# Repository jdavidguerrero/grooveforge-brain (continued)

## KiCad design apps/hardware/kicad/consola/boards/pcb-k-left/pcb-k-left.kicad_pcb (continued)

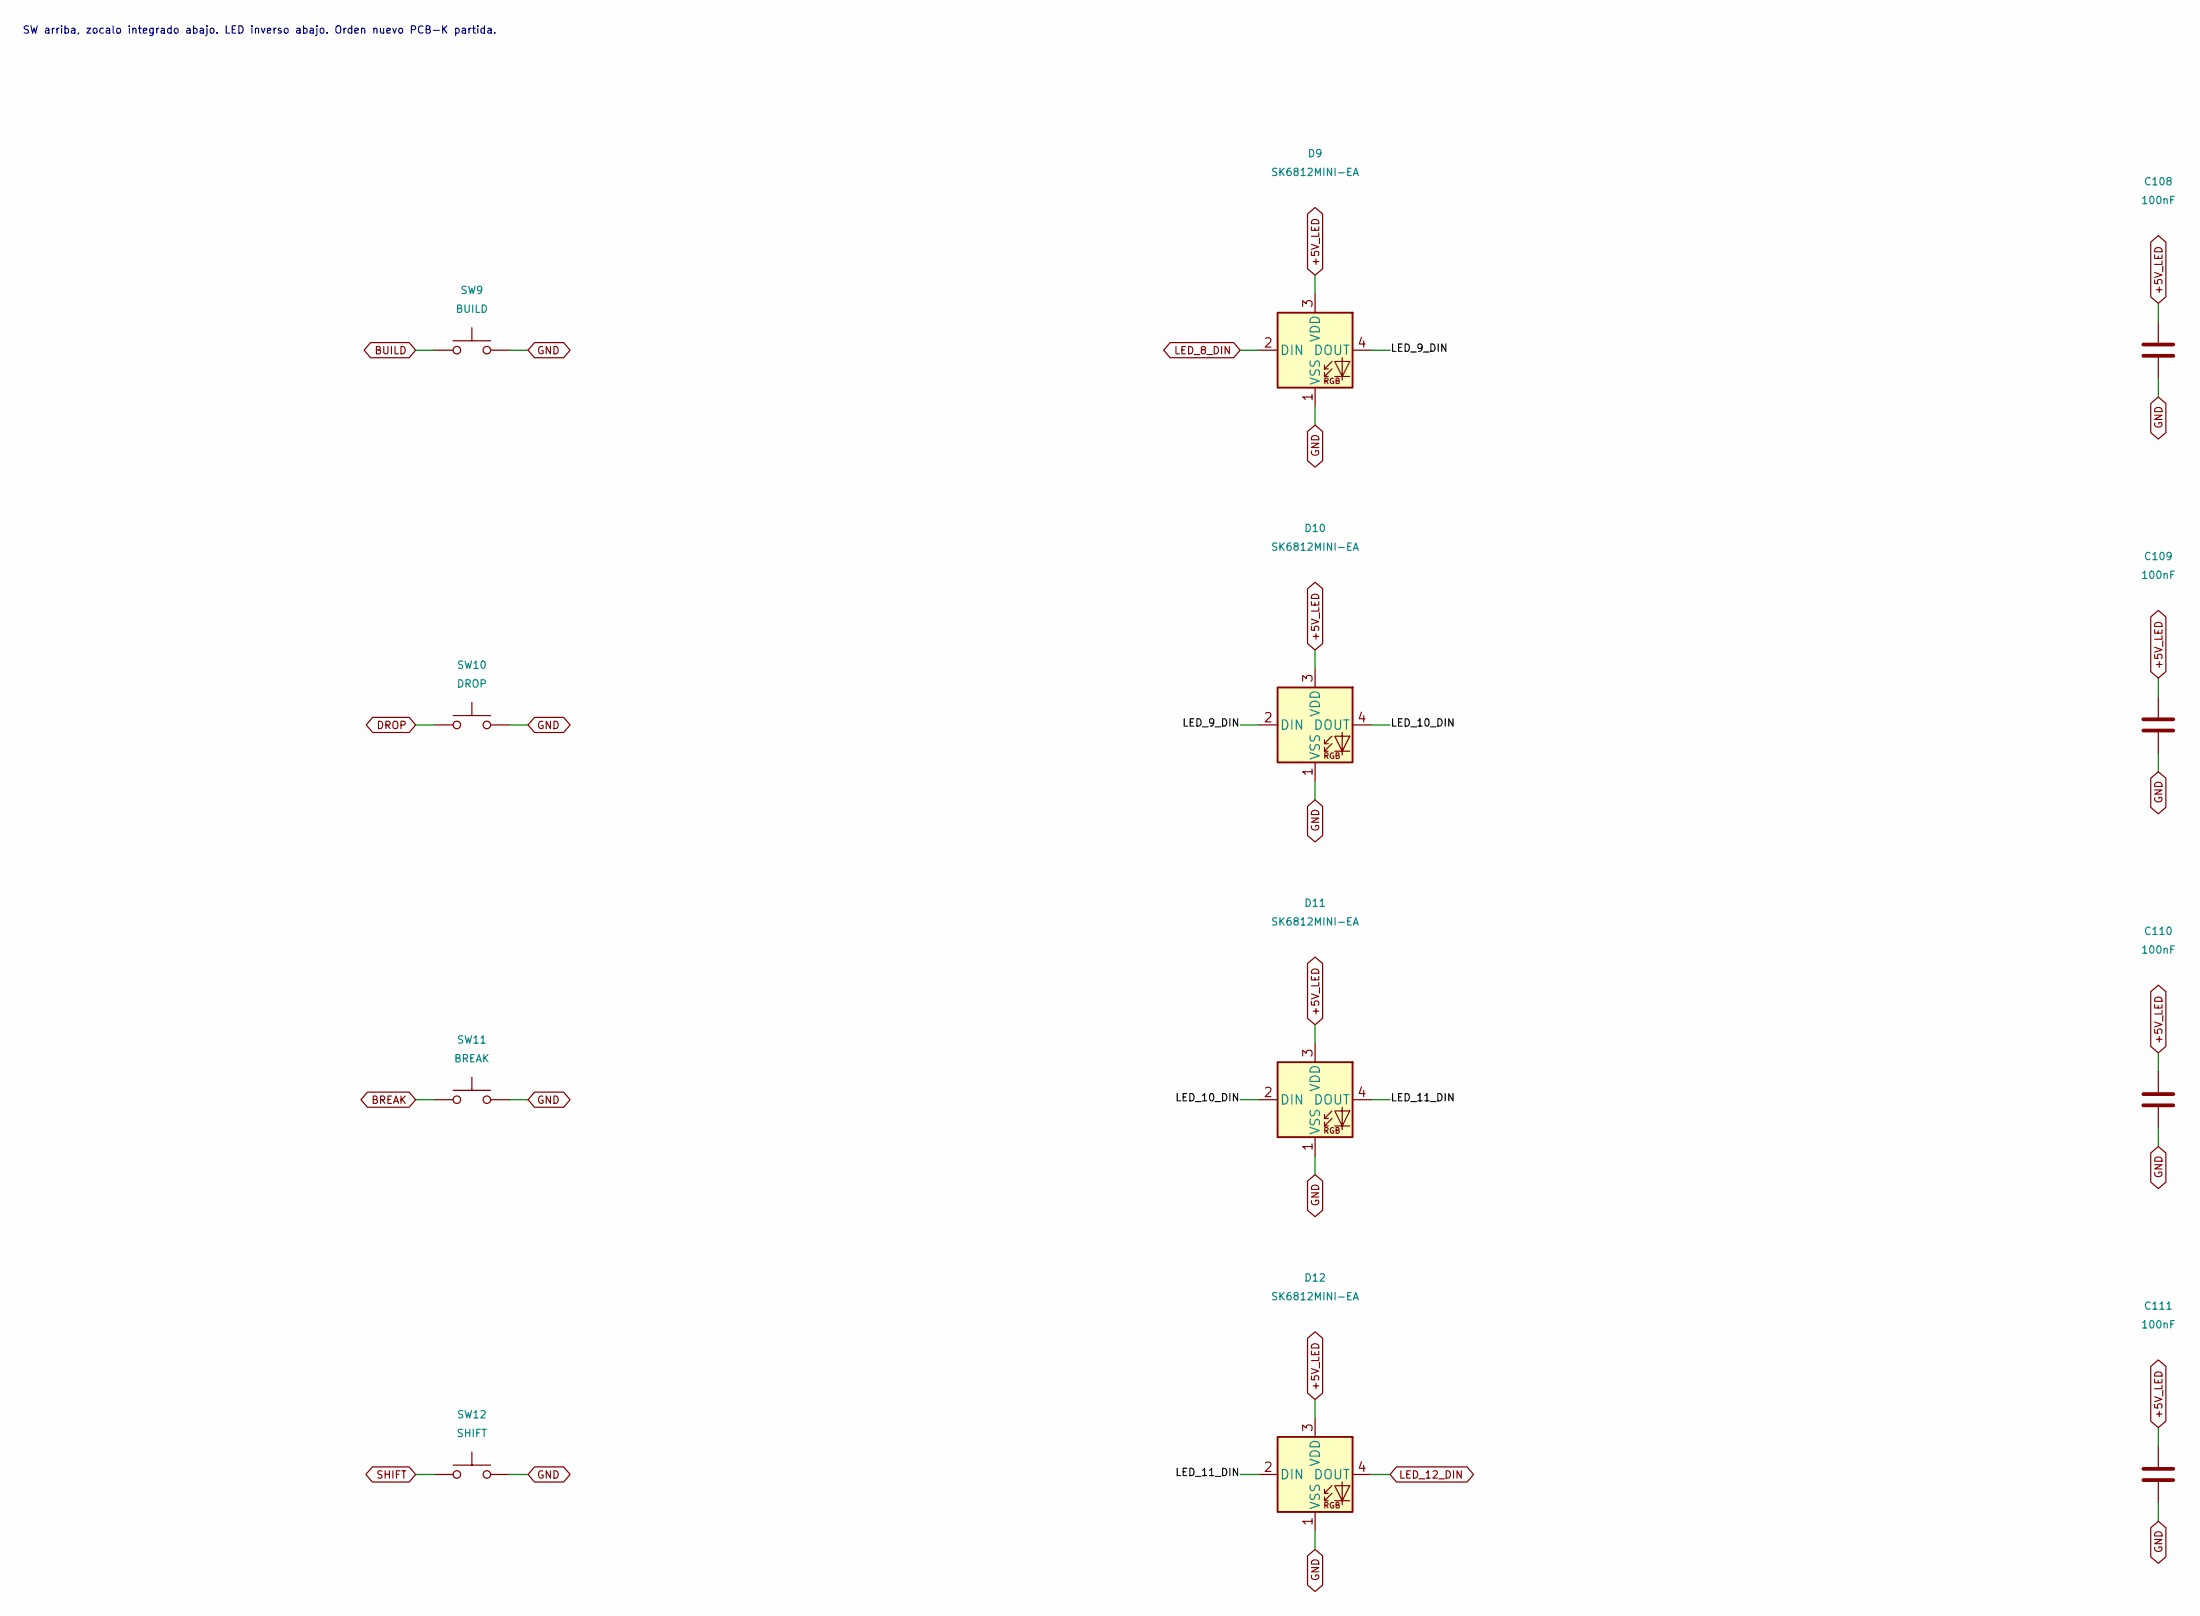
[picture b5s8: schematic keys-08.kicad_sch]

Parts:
C108, C109, C110, C111: 100nF; C_0805_2012Metric; MPN CC0805KRX7R9BB104; LCSC C49678
D9, D10, D11, D12: SK6812MINI-EA; SK6812MINI-EA_ReverseMount; MPN SK6812MINI-EA; LCSC C5378731
SW9: BUILD; Kailh_Choc_V2_PG1353_Hotswap
SW10: DROP; Kailh_Choc_V2_PG1353_Hotswap
SW11: BREAK; Kailh_Choc_V2_PG1353_Hotswap
SW12: SHIFT; Kailh_Choc_V2_PG1353_Hotswap

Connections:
+5V_LED: C108.1, C109.1, C110.1, C111.1, D9.3 (VDD), D10.3 (VDD), D11.3 (VDD), D12.3 (VDD); also elsewhere on the board
/keys-08/LED_9_DIN: D9.4 (DOUT), D10.2 (DIN)
/keys-08/LED_10_DIN: D10.4 (DOUT), D11.2 (DIN)
/keys-08/LED_11_DIN: D11.4 (DOUT), D12.2 (DIN)
BREAK: SW11.1; also elsewhere on the board
BUILD: SW9.1; also elsewhere on the board
DROP: SW10.1; also elsewhere on the board
GND: C108.2, C109.2, C110.2, C111.2, D9.1 (VSS), D10.1 (VSS), D11.1 (VSS), D12.1 (VSS), SW9.2, SW10.2, SW11.2, SW12.2; also elsewhere on the board
LED_8_DIN: D9.2 (DIN); also elsewhere on the board
LED_12_DIN: D12.4 (DOUT); also elsewhere on the board
SHIFT: SW12.1; also elsewhere on the board

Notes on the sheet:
SW arriba, zocalo integrado abajo. LED inverso abajo. Orden nuevo PCB-K partida.

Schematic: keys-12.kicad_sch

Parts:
C112, C113, C114, C115: 100nF; C_0805_2012Metric; MPN CC0805KRX7R9BB104; LCSC C49678
D13, D14, D15, D16: SK6812MINI-EA; SK6812MINI-EA_ReverseMount; MPN SK6812MINI-EA; LCSC C5378731
SW13: UNDO; Kailh_Choc_V2_PG1353_Hotswap
SW14: DELETE; Kailh_Choc_V2_PG1353_Hotswap
SW15: DUPLICATE; Kailh_Choc_V2_PG1353_Hotswap
SW16: QUANTIZE; Kailh_Choc_V2_PG1353_Hotswap

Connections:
+5V_LED: C112.1, C113.1, C114.1, C115.1, D13.3 (VDD), D14.3 (VDD), D15.3 (VDD), D16.3 (VDD); also elsewhere on the board
/keys-12/LED_13_DIN: D13.4 (DOUT), D14.2 (DIN)
/keys-12/LED_14_DIN: D14.4 (DOUT), D15.2 (DIN)
/keys-12/LED_15_DIN: D15.4 (DOUT), D16.2 (DIN)
DELETE: SW14.1; also elsewhere on the board
DUPLICATE: SW15.1; also elsewhere on the board
GND: C112.2, C113.2, C114.2, C115.2, D13.1 (VSS), D14.1 (VSS), D15.1 (VSS), D16.1 (VSS), SW13.2, SW14.2, SW15.2, SW16.2; also elsewhere on the board
LED_12_DIN: D13.2 (DIN); also elsewhere on the board
LED_16_DIN: D16.4 (DOUT); also elsewhere on the board
QUANTIZE: SW16.1; also elsewhere on the board
UNDO: SW13.1; also elsewhere on the board

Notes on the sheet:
SW arriba, zocalo integrado abajo. LED inverso abajo. Orden nuevo PCB-K partida.

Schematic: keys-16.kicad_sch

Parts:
C116: 100nF; C_0805_2012Metric; MPN CC0805KRX7R9BB104; LCSC C49678
D17: SK6812MINI-EA; SK6812MINI-EA_ReverseMount; MPN SK6812MINI-EA; LCSC C5378731
SW17: NEW; Kailh_Choc_V2_PG1353_Hotswap

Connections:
+5V_LED: C116.1, D17.3 (VDD); also elsewhere on the board
GND: C116.2, D17.1 (VSS), SW17.2; also elsewhere on the board
LED_16_DIN: D17.2 (DIN); also elsewhere on the board
LED_DATA: D17.4 (DOUT); also elsewhere on the board
NEW: SW17.1; also elsewhere on the board

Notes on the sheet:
SW arriba, zocalo integrado abajo. LED inverso abajo. Orden nuevo PCB-K partida.

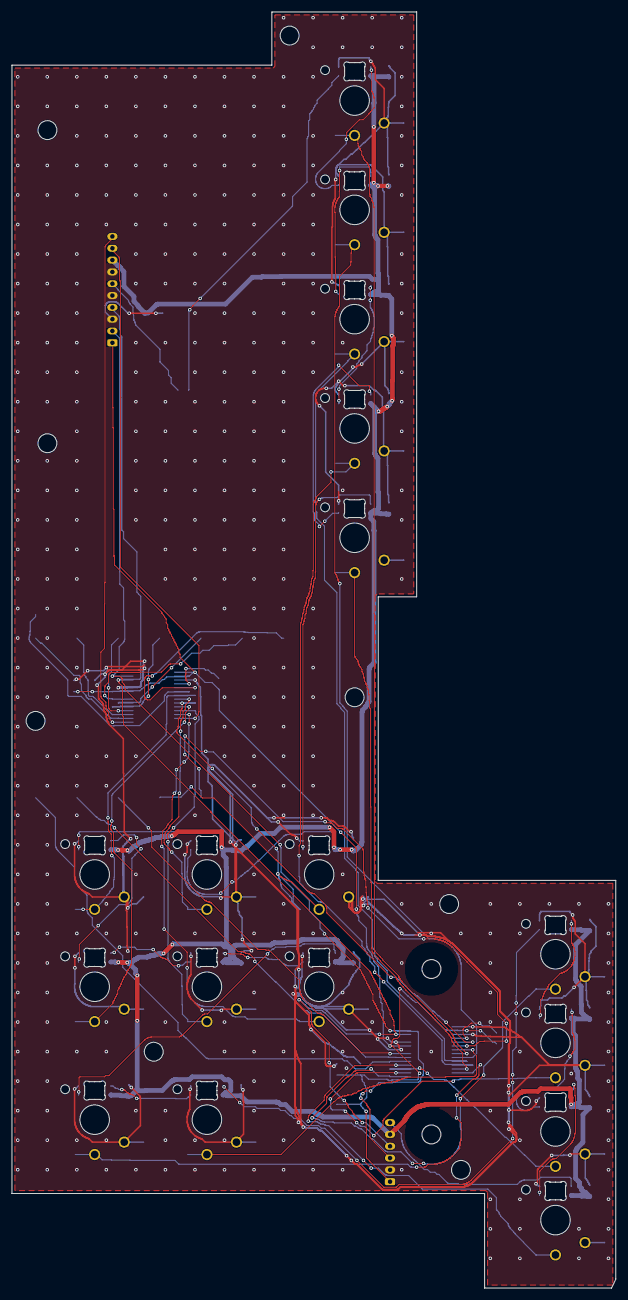
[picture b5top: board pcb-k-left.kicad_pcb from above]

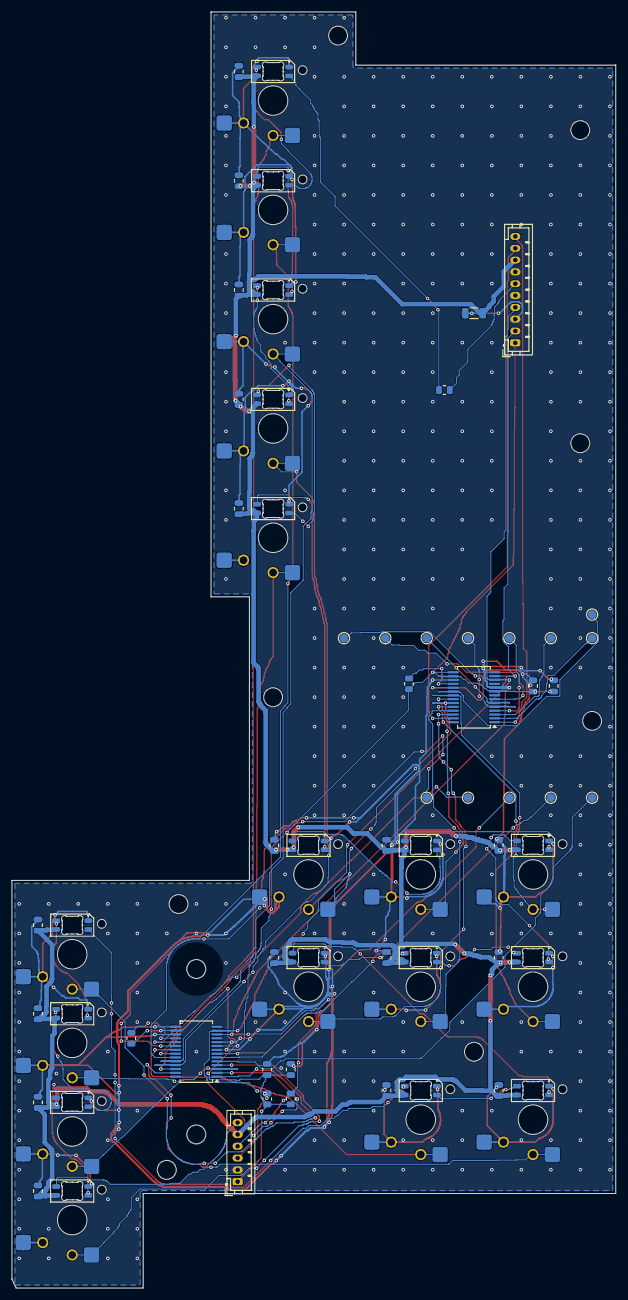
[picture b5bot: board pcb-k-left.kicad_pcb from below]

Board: 2 copper layers, 102.2 x 216.0 mm, 88 parts (61 on the bottom side), 58 nets.

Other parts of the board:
H1, H2, H3, H4, H5, H6, H7, H8, H9, H10: M2.5 PEM

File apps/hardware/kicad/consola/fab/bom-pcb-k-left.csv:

"Reference","Value","Footprint","LCSC","Supply","SupplyDescription","DNP"
"C1","22uF","Capacitor_SMD:C_1206_3216Metric","C12891","","",""
"C100","100nF","Capacitor_SMD:C_0805_2012Metric","C49678","","",""
"C101","100nF","Capacitor_SMD:C_0805_2012Metric","C49678","","",""
"C102","100nF","Capacitor_SMD:C_0805_2012Metric","C49678","","",""
"C103","100nF","Capacitor_SMD:C_0805_2012Metric","C49678","","",""
"C104","100nF","Capacitor_SMD:C_0805_2012Metric","C49678","","",""
"C105","100nF","Capacitor_SMD:C_0805_2012Metric","C49678","","",""
"C106","100nF","Capacitor_SMD:C_0805_2012Metric","C49678","","",""
"C107","100nF","Capacitor_SMD:C_0805_2012Metric","C49678","","",""
"C108","100nF","Capacitor_SMD:C_0805_2012Metric","C49678","","",""
"C109","100nF","Capacitor_SMD:C_0805_2012Metric","C49678","","",""
"C110","100nF","Capacitor_SMD:C_0805_2012Metric","C49678","","",""
"C111","100nF","Capacitor_SMD:C_0805_2012Metric","C49678","","",""
"C112","100nF","Capacitor_SMD:C_0805_2012Metric","C49678","","",""
"C113","100nF","Capacitor_SMD:C_0805_2012Metric","C49678","","",""
"C114","100nF","Capacitor_SMD:C_0805_2012Metric","C49678","","",""
"C115","100nF","Capacitor_SMD:C_0805_2012Metric","C49678","","",""
"C116","100nF","Capacitor_SMD:C_0805_2012Metric","C49678","","",""
"C221","100nF","Capacitor_SMD:C_0805_2012Metric","C49678","","",""
"C222","1uF","Capacitor_SMD:C_0805_2012Metric","C5137478","","",""
"C231","100nF","Capacitor_SMD:C_0805_2012Metric","C49678","","",""
"C232","1uF","Capacitor_SMD:C_0805_2012Metric","C5137478","","",""
"D1","SK6812MINI-EA","gf_consola:SK6812MINI-EA_ReverseMount","C5378731","","",""
"D2","SK6812MINI-EA","gf_consola:SK6812MINI-EA_ReverseMount","C5378731","","",""
"D3","SK6812MINI-EA","gf_consola:SK6812MINI-EA_ReverseMount","C5378731","","",""
"D4","SK6812MINI-EA","gf_consola:SK6812MINI-EA_ReverseMount","C5378731","","",""
"D5","SK6812MINI-EA","gf_consola:SK6812MINI-EA_ReverseMount","C5378731","","",""
"D6","SK6812MINI-EA","gf_consola:SK6812MINI-EA_ReverseMount","C5378731","","",""
"D7","SK6812MINI-EA","gf_consola:SK6812MINI-EA_ReverseMount","C5378731","","",""
"D8","SK6812MINI-EA","gf_consola:SK6812MINI-EA_ReverseMount","C5378731","","",""
"D9","SK6812MINI-EA","gf_consola:SK6812MINI-EA_ReverseMount","C5378731","","",""
"D10","SK6812MINI-EA","gf_consola:SK6812MINI-EA_ReverseMount","C5378731","","",""
"D11","SK6812MINI-EA","gf_consola:SK6812MINI-EA_ReverseMount","C5378731","","",""
"D12","SK6812MINI-EA","gf_consola:SK6812MINI-EA_ReverseMount","C5378731","","",""
"D13","SK6812MINI-EA","gf_consola:SK6812MINI-EA_ReverseMount","C5378731","","",""
"D14","SK6812MINI-EA","gf_consola:SK6812MINI-EA_ReverseMount","C5378731","","",""
"D15","SK6812MINI-EA","gf_consola:SK6812MINI-EA_ReverseMount","C5378731","","",""
"D16","SK6812MINI-EA","gf_consola:SK6812MINI-EA_ReverseMount","C5378731","","",""
"D17","SK6812MINI-EA","gf_consola:SK6812MINI-EA_ReverseMount","C5378731","","",""
"J1","PCB-M","Connector_JST:JST_PH_B10B-PH-K_1x10_P2.00mm_Vertical","C158038","","",""
"J2","HACIA DERECHA","Connector_JST:JST_PH_B6B-PH-K_1x06_P2.00mm_Vertical","C131342","","",""
"R1","33R","Resistor_SMD:R_0805_2012Metric","C17634","","",""
"R2","2.2k DNP","Resistor_SMD:R_0805_2012Metric","C17520","","","DNP"
"R3","2.2k DNP","Resistor_SMD:R_0805_2012Metric","C17520","","","DNP"
"R22","10k","Resistor_SMD:R_0805_2012Metric","C17414","","",""
"R23","10k","Resistor_SMD:R_0805_2012Metric","C17414","","",""
"SW1","BACK","gf_consola:Kailh_Choc_V2_PG1353_Hotswap","","owner","Juan: tecla Kailh Choc V2 PG1353 + zócalo Kailh CPG135001S30 comprado aparte por AliExpress",""
"SW2","MENU","gf_consola:Kailh_Choc_V2_PG1353_Hotswap","","owner","Juan: tecla Kailh Choc V2 PG1353 + zócalo Kailh CPG135001S30 comprado aparte por AliExpress",""
"SW3","NAV_L","gf_consola:Kailh_Choc_V2_PG1353_Hotswap","","owner","Juan: tecla Kailh Choc V2 PG1353 + zócalo Kailh CPG135001S30 comprado aparte por AliExpress",""
"SW4","NAV_R","gf_consola:Kailh_Choc_V2_PG1353_Hotswap","","owner","Juan: tecla Kailh Choc V2 PG1353 + zócalo Kailh CPG135001S30 comprado aparte por AliExpress",""
"SW5","BROWSE","gf_consola:Kailh_Choc_V2_PG1353_Hotswap","","owner","Juan: tecla Kailh Choc V2 PG1353 + zócalo Kailh CPG135001S30 comprado aparte por AliExpress",""
"SW6","TAP","gf_consola:Kailh_Choc_V2_PG1353_Hotswap","","owner","Juan: tecla Kailh Choc V2 PG1353 + zócalo Kailh CPG135001S30 comprado aparte por AliExpress",""
"SW7","FILL","gf_consola:Kailh_Choc_V2_PG1353_Hotswap","","owner","Juan: tecla Kailh Choc V2 PG1353 + zócalo Kailh CPG135001S30 comprado aparte por AliExpress",""
"SW8","CUE_ENG","gf_consola:Kailh_Choc_V2_PG1353_Hotswap","","owner","Juan: tecla Kailh Choc V2 PG1353 + zócalo Kailh CPG135001S30 comprado aparte por AliExpress",""
"SW9","BUILD","gf_consola:Kailh_Choc_V2_PG1353_Hotswap","","owner","Juan: tecla Kailh Choc V2 PG1353 + zócalo Kailh CPG135001S30 comprado aparte por AliExpress",""
"SW10","DROP","gf_consola:Kailh_Choc_V2_PG1353_Hotswap","","owner","Juan: tecla Kailh Choc V2 PG1353 + zócalo Kailh CPG135001S30 comprado aparte por AliExpress",""
"SW11","BREAK","gf_consola:Kailh_Choc_V2_PG1353_Hotswap","","owner","Juan: tecla Kailh Choc V2 PG1353 + zócalo Kailh CPG135001S30 comprado aparte por AliExpress",""
"SW12","SHIFT","gf_consola:Kailh_Choc_V2_PG1353_Hotswap","","owner","Juan: tecla Kailh Choc V2 PG1353 + zócalo Kailh CPG135001S30 comprado aparte por AliExpress",""
"SW13","UNDO","gf_consola:Kailh_Choc_V2_PG1353_Hotswap","","owner","Juan: tecla Kailh Choc V2 PG1353 + zócalo Kailh CPG135001S30 comprado aparte por AliExpress",""
"SW14","DELETE","gf_consola:Kailh_Choc_V2_PG1353_Hotswap","","owner","Juan: tecla Kailh Choc V2 PG1353 + zócalo Kailh CPG135001S30 comprado aparte por AliExpress",""
"SW15","DUPLICATE","gf_consola:Kailh_Choc_V2_PG1353_Hotswap","","owner","Juan: tecla Kailh Choc V2 PG1353 + zócalo Kailh CPG135001S30 comprado aparte por AliExpress",""
"SW16","QUANTIZE","gf_consola:Kailh_Choc_V2_PG1353_Hotswap","","owner","Juan: tecla Kailh Choc V2 PG1353 + zócalo Kailh CPG135001S30 comprado aparte por AliExpress",""
"SW17","NEW","gf_consola:Kailh_Choc_V2_PG1353_Hotswap","","owner","Juan: tecla Kailh Choc V2 PG1353 + zócalo Kailh CPG135001S30 comprado aparte por AliExpress",""
"TP225","SPARE_22_GPB4","TestPoint:TestPoint_Pad_D1.5mm","","","",""
"TP226","SPARE_22_GPB5","TestPoint:TestPoint_Pad_D1.5mm","","","",""
"TP227","SPARE_22_GPB6","TestPoint:TestPoint_Pad_D1.5mm","","","",""
"TP232","SPARE_23_GPB1","TestPoint:TestPoint_Pad_D1.5mm","","","",""
"TP233","SPARE_23_GPB2","TestPoint:TestPoint_Pad_D1.5mm","","","",""
"TP234","SPARE_23_GPB3","TestPoint:TestPoint_Pad_D1.5mm","","","",""
"TP235","SPARE_23_GPB4","TestPoint:TestPoint_Pad_D1.5mm","","","",""
"TP236","SPARE_23_GPB5","TestPoint:TestPoint_Pad_D1.5mm","","","",""
"TP237","SPARE_23_GPB6","TestPoint:TestPoint_Pad_D1.5mm","","","",""
"TP2219","INTB_22","TestPoint:TestPoint_Pad_D1.5mm","","","",""
"TP2220","INTA_22","TestPoint:TestPoint_Pad_D1.5mm","","","",""
"TP2319","INTB_23","TestPoint:TestPoint_Pad_D1.5mm","","","",""
"TP2320","INTA_23","TestPoint:TestPoint_Pad_D1.5mm","","","",""
"U22","MCP23017-E/SS 0x22","Package_SO:SSOP-28_5.3x10.2mm_P0.65mm","C506653","","",""
"U23","MCP23017-E/SS 0x23","Package_SO:SSOP-28_5.3x10.2mm_P0.65mm","C506653","","",""

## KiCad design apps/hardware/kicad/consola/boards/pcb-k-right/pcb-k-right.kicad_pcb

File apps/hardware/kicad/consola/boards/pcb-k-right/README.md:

# PCB-K derecha — GrooveForge Console

Layout terminado de dos capas y 1,6 mm; DRC entregado con **0 errores, 0 sin conectar y 0 diferencias de paridad**.
Los avisos de huella/serigrafía y las comprobaciones físicas pendientes se detallan en
[REPORT-k](../../tools/layout/REPORT-k.md). Este estado no equivale a aprobación CAM ni a validación del lote real.

La placa guardada es `pcb-k-right.kicad_pcb`; los Gerbers, taladros y el ZIP para PCB desnuda están en
[fab/](fab/). Usar esta entrega local, junto con su DRC en `docs/`, como fuente de fabricación.
`docs/` contiene además XML, PDF y ERC. Ver [doc 28](../../../../../docs/consola/28-pcb-k.md) para montaje.

`placement.csv` usa mm de panel, vista superior, +y hacia atrás. La transformación del layout es
**x_panel = x_KiCad + 44; y_panel = 371 − y_KiCad**. Rotaciones CCW KiCad; F = superior, B = inferior.
El LED queda a +4,93 mm del centro de tecla en y_panel. Las demás piezas van abajo.
Los soportes y los cuatro anclajes del marco M4 están definidos en el CSV de contornos y doc 28 §2.

## Montaje

**Choc V2 SOLDADAS directamente, sin zócalos**, según doc 28 **D-K1b** (Juan, 2026-11-13).
Las filas históricas key/socket de igual referencia representan una única huella mixta;
no comprar ni montar zócalos CPG135001S30. Los pads SMD asociados quedan sin uso.

Los JST PH THT **J1** van en la cara B: **recortar las colas a ≤0,8 mm sobre la cara de soldadura**
(cara superior, hacia la chapa). El máximo incluye todo metal y soldadura. Verificar cada pin con
calibre de altura o galga apoyada en el FR4 después de soldar y recortar; eliminar rebabas y comprobar
que ningún pico exceda 0,8 mm. Registrar la altura máxima antes de montar contra el aluminio.
La luz nominal a la chapa es solo **1,4 mm**, por lo que quedan **0,6 mm nominales**; comprobar también
la separación final con las tolerancias del apilado. No aceptar contacto con la chapa.

Para verificar el esquema desde la raíz: `python3 apps/hardware/kicad/consola/tools/check_netlist.py --board pcb-k-right`.

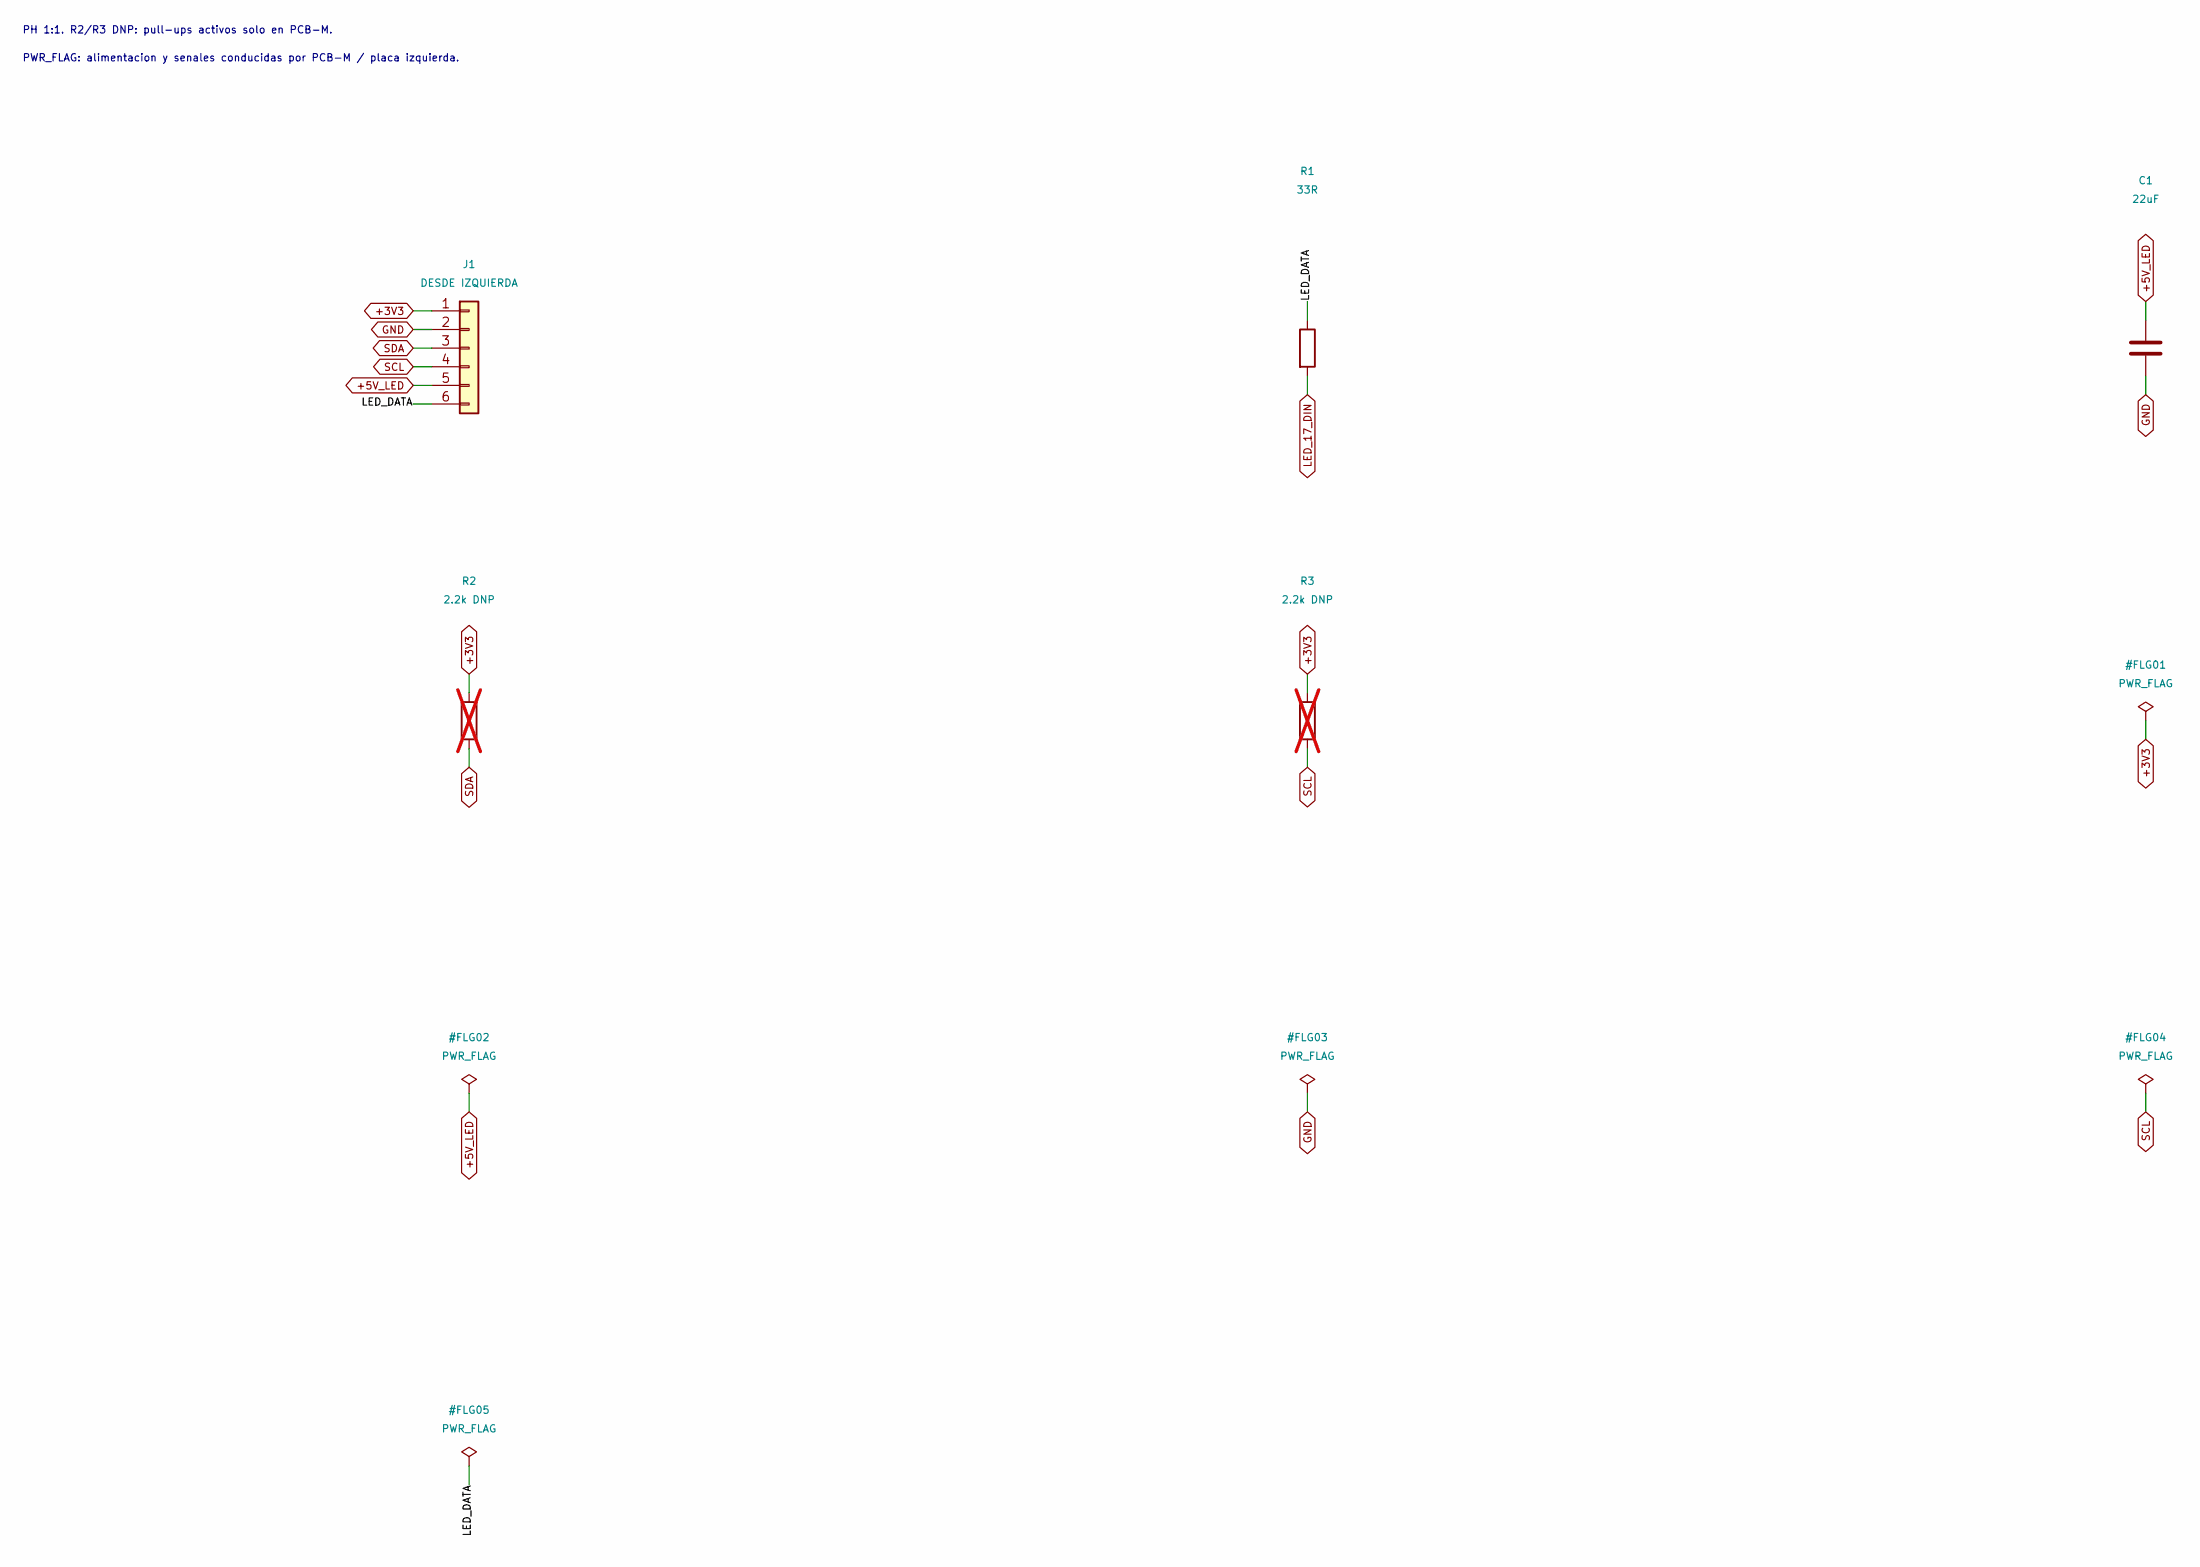
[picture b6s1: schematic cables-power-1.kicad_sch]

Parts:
C1: 22uF; C_1206_3216Metric; MPN CL31A226KAHNNNE; LCSC C12891
J1: DESDE IZQUIERDA; JST_PH_B6B-PH-K_1x06_P2.00mm_Vertical; MPN B6B-PH-K-S(LF)(SN); LCSC C131342
R1: 33R; R_0805_2012Metric; MPN 0805W8F330JT5E; LCSC C17634
R2, R3: 2.2k DNP; R_0805_2012Metric; MPN 0805W8F2201T5E; LCSC C17520; not fitted

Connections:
+3V3: J1.1, R2.1, R3.1; also elsewhere on the board
+5V_LED: C1.1, J1.5; also elsewhere on the board
/cables-power-1/LED_DATA: J1.6, R1.1
GND: C1.2, J1.2; also elsewhere on the board
LED_17_DIN: R1.2; also elsewhere on the board
SCL: J1.4, R3.2; also elsewhere on the board
SDA: J1.3, R2.2; also elsewhere on the board

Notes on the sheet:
PH 1:1. R2/R3 DNP: pull-ups activos solo en PCB-M.
PWR_FLAG: alimentacion y senales conducidas por PCB-M / placa izquierda.

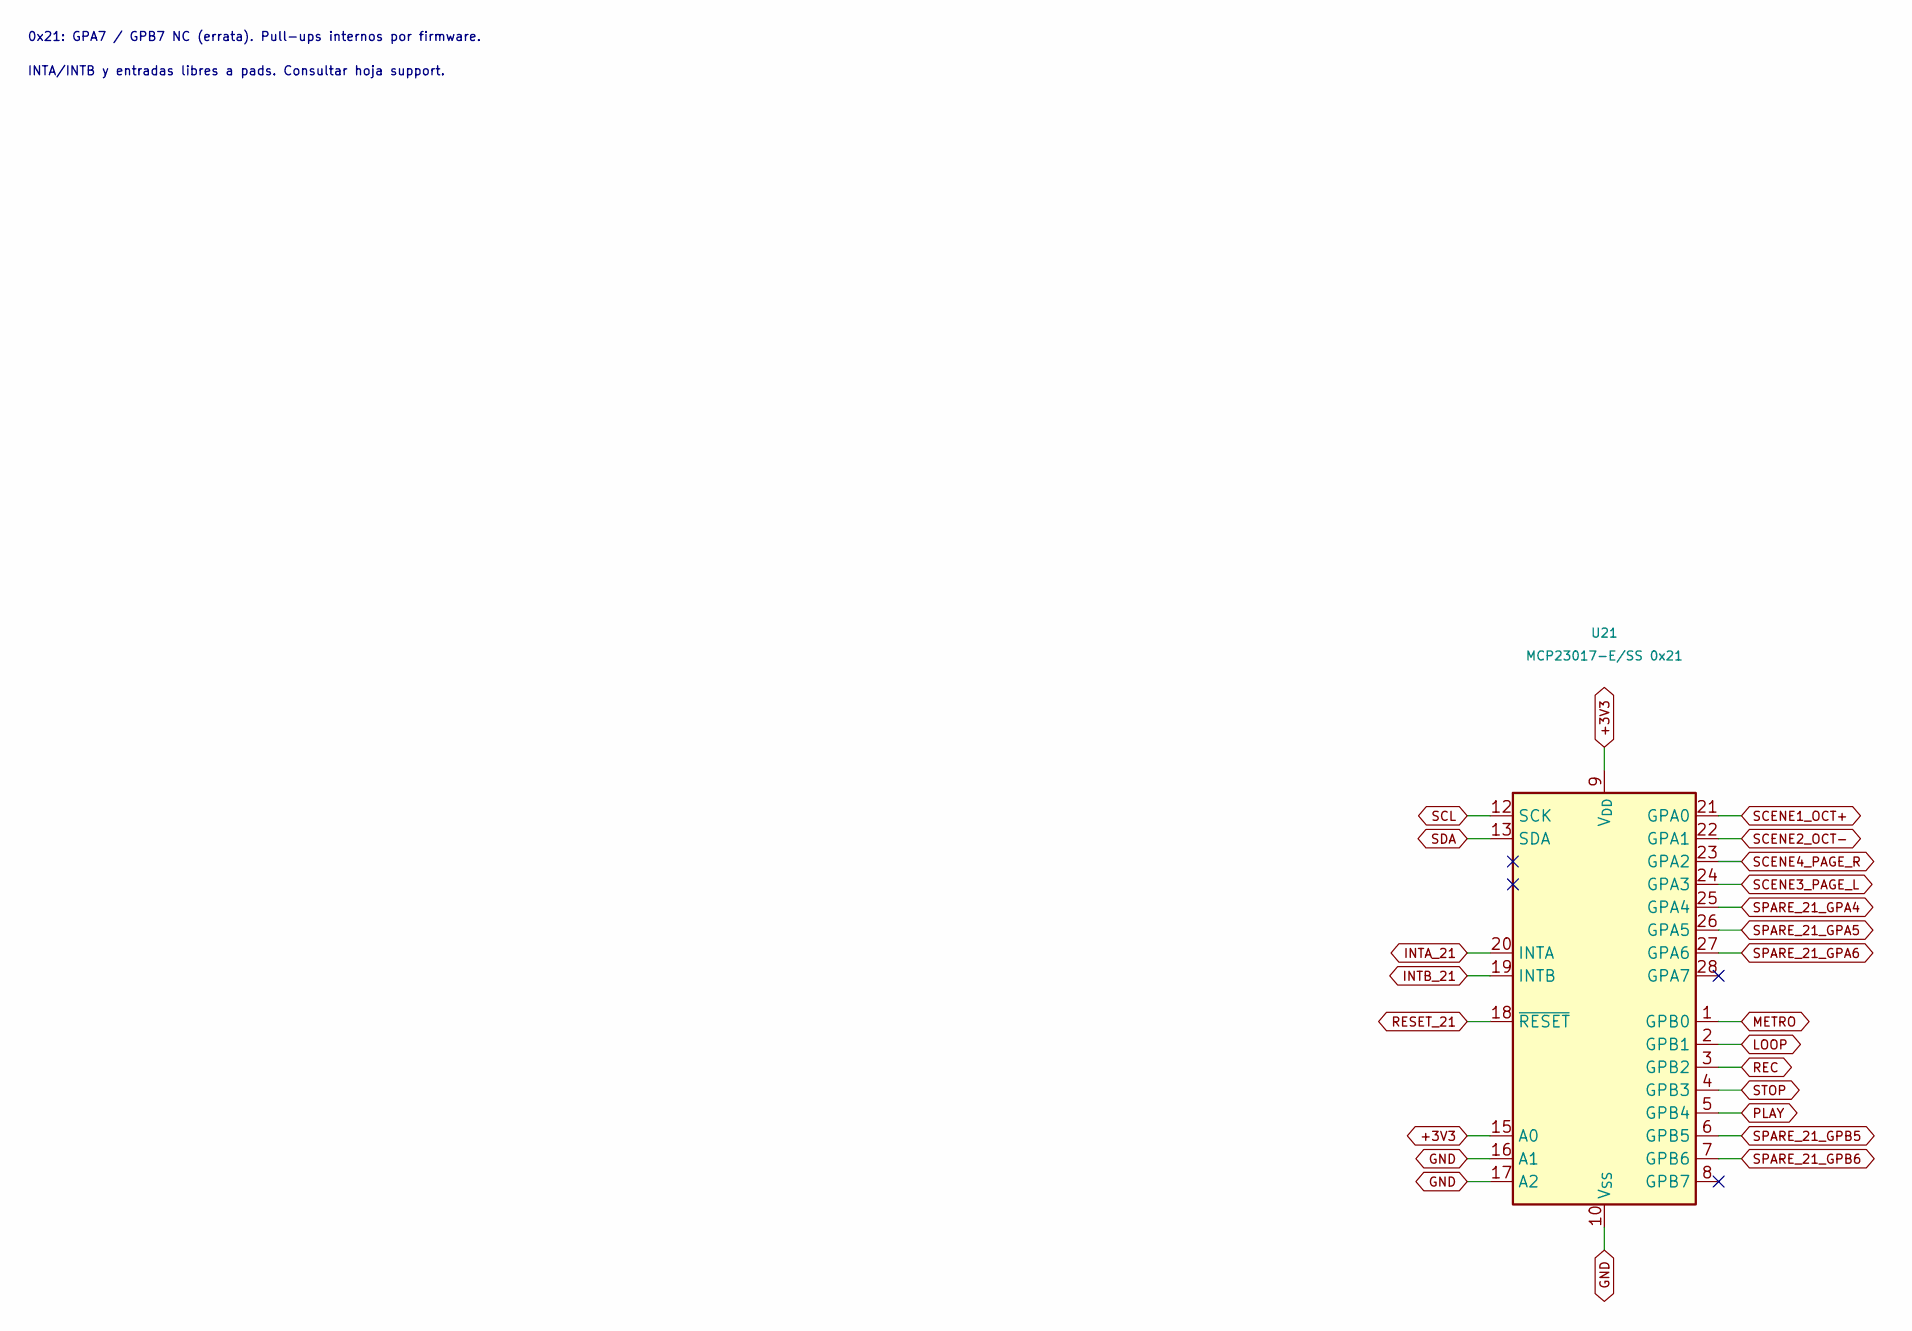
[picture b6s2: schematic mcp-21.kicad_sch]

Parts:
U21: MCP23017-E/SS 0x21; SSOP-28_5.3x10.2mm_P0.65mm; MPN MCP23017-E/SS; LCSC C506653

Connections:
+3V3: U21.9 (V_{DD}), U21.15 (A0); also elsewhere on the board
GND: U21.10 (V_{SS}), U21.16 (A1), U21.17 (A2); also elsewhere on the board
INTA_21: U21.20 (INTA); also elsewhere on the board
INTB_21: U21.19 (INTB); also elsewhere on the board
LOOP: U21.2 (GPB1); also elsewhere on the board
METRO: U21.1 (GPB0); also elsewhere on the board
PLAY: U21.5 (GPB4); also elsewhere on the board
REC: U21.3 (GPB2); also elsewhere on the board
RESET_21: U21.18 (~RESET); also elsewhere on the board
SCENE1_OCT+: U21.21 (GPA0); also elsewhere on the board
SCENE2_OCT-: U21.22 (GPA1); also elsewhere on the board
SCENE3_PAGE_L: U21.24 (GPA3); also elsewhere on the board
SCENE4_PAGE_R: U21.23 (GPA2); also elsewhere on the board
SCL: U21.12 (SCK); also elsewhere on the board
SDA: U21.13 (SDA); also elsewhere on the board
SPARE_21_GPA4: U21.25 (GPA4); also elsewhere on the board
SPARE_21_GPA5: U21.26 (GPA5); also elsewhere on the board
SPARE_21_GPA6: U21.27 (GPA6); also elsewhere on the board
SPARE_21_GPB5: U21.6 (GPB5); also elsewhere on the board
SPARE_21_GPB6: U21.7 (GPB6); also elsewhere on the board
STOP: U21.4 (GPB3); also elsewhere on the board

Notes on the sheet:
0x21: GPA7 / GPB7 NC (errata). Pull-ups internos por firmware.
INTA/INTB y entradas libres a pads. Consultar hoja support.
